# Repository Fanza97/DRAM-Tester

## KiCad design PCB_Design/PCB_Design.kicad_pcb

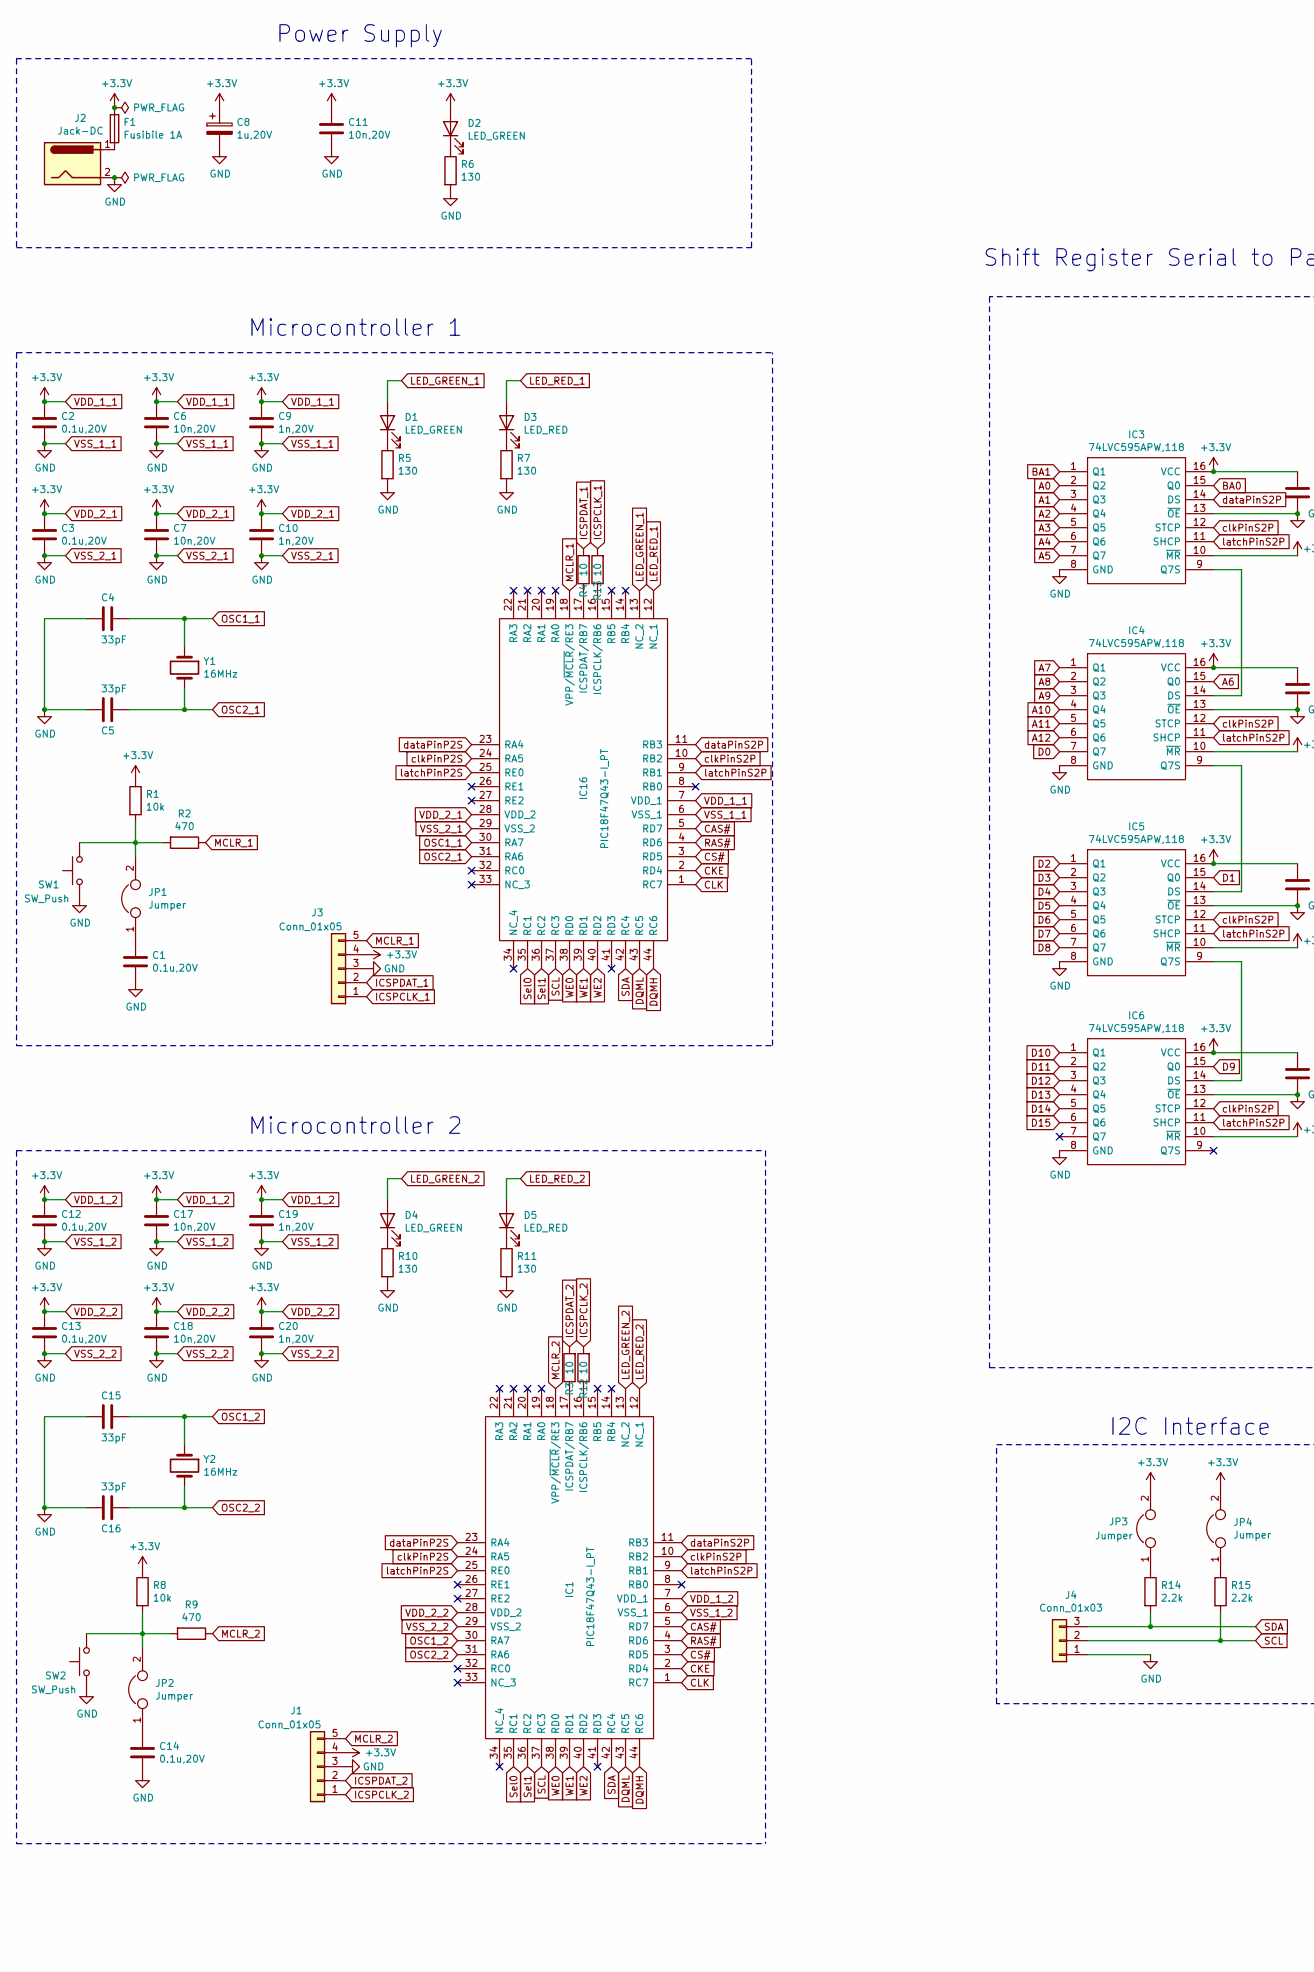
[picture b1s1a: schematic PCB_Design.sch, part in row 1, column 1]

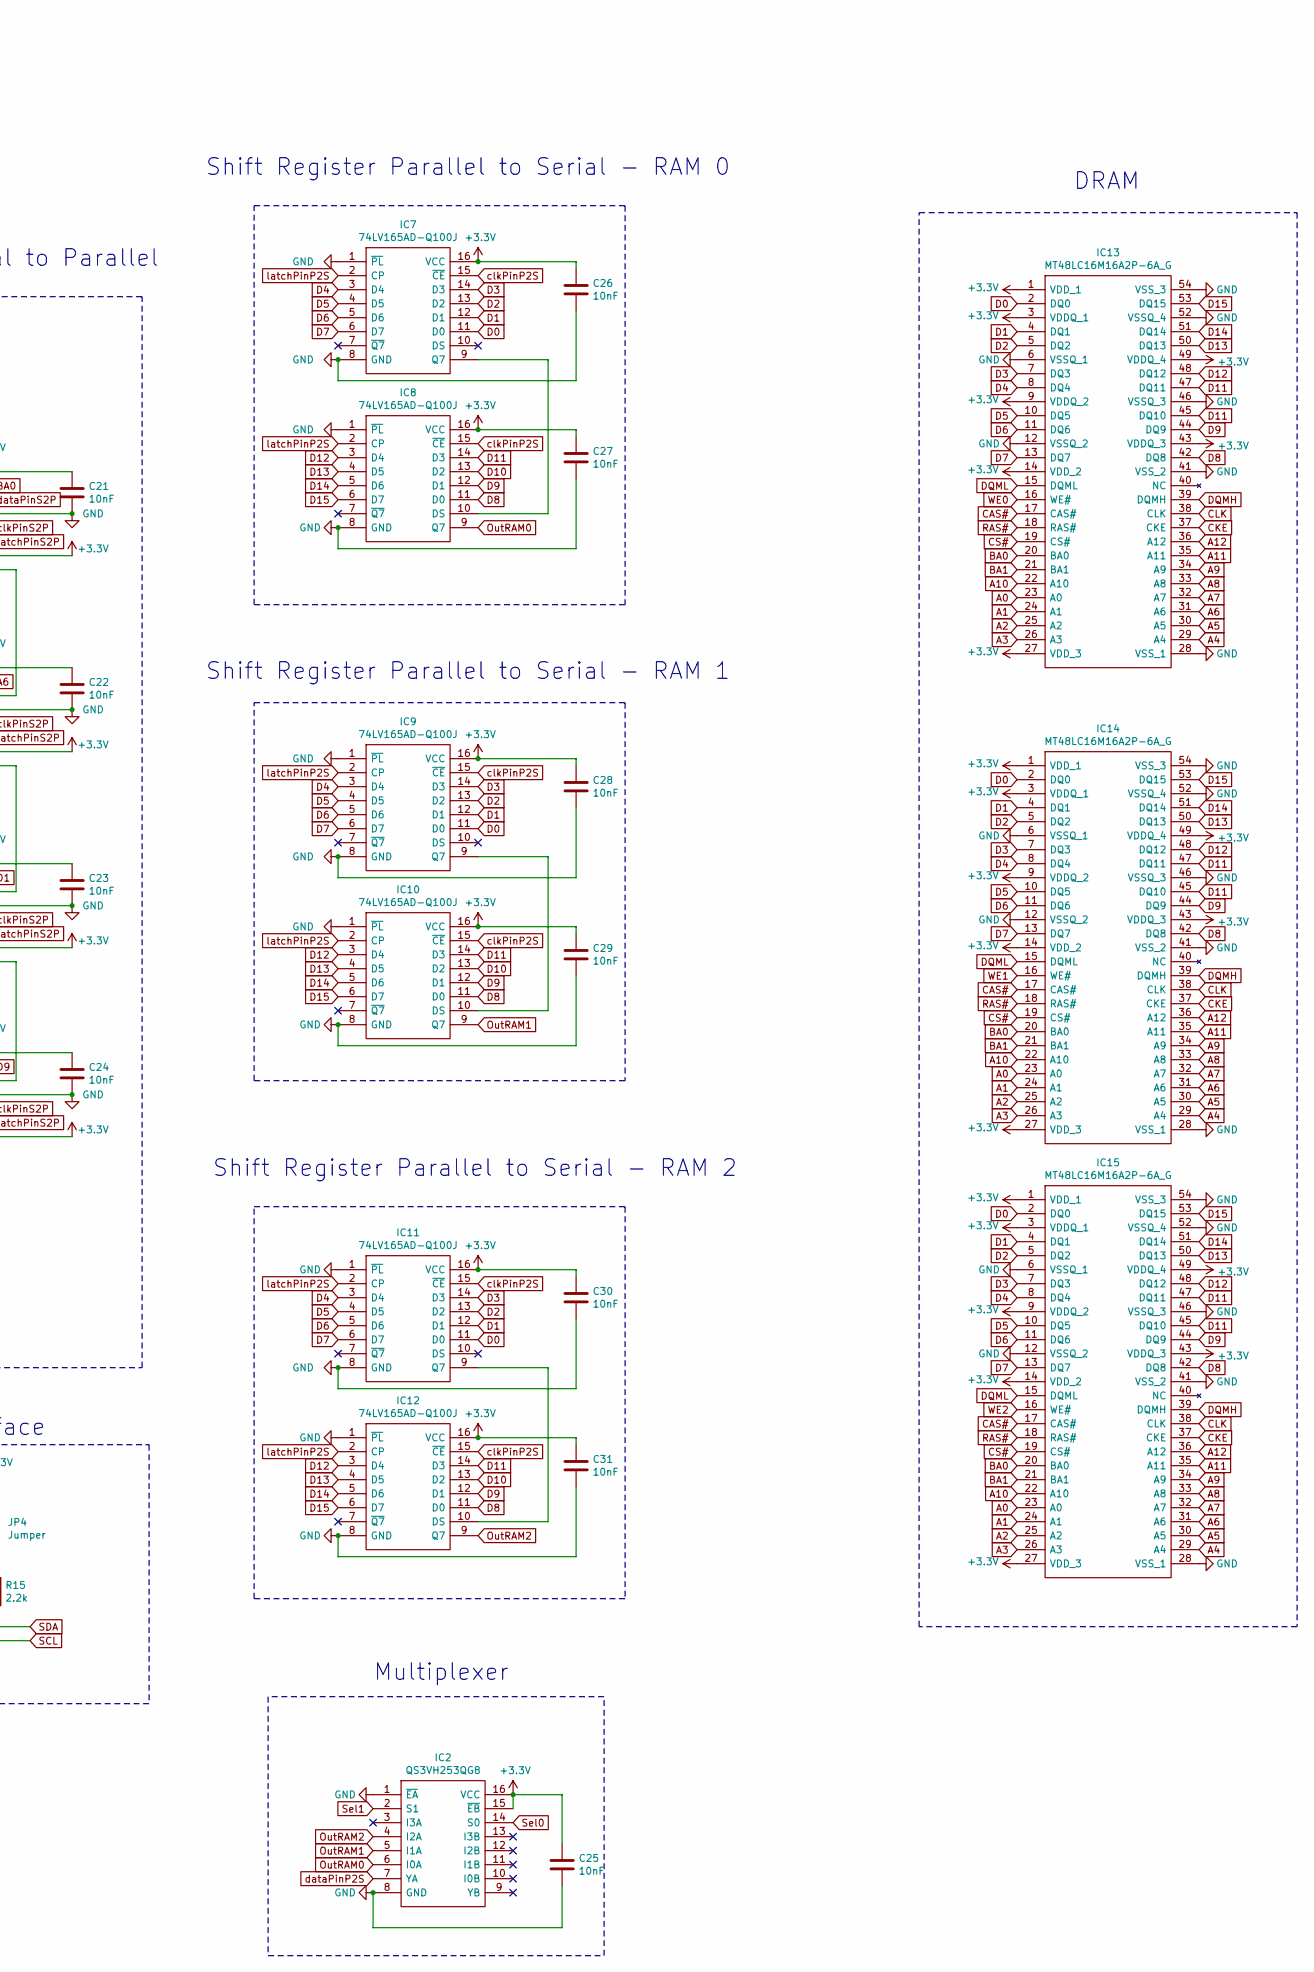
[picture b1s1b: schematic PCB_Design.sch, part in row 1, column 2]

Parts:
C1, C2, C3, C12, C13, C14: 0.1u,20V; C_0805_2012Metric_Pad1.15x1.40mm_HandSolder
C4, C5, C15, C16: 33pF; C_0805_2012Metric_Pad1.15x1.40mm_HandSolder
C6, C7, C11, C17, C18: 10n,20V; C_0805_2012Metric_Pad1.15x1.40mm_HandSolder
C8: 1u,20V; CP_Elec_4x4.5
C9, C10, C19, C20: 1n,20V; C_0805_2012Metric_Pad1.15x1.40mm_HandSolder
C21, C22, C23, C24, C25, C26, C27, C28, C29, C30, C31: 10nF; C_0805_2012Metric_Pad1.15x1.40mm_HandSolder
D1, D2, D4: LED_GREEN; LED_0805_2012Metric_Pad1.15x1.40mm_HandSolder
D3, D5: LED_RED; LED_0805_2012Metric_Pad1.15x1.40mm_HandSolder
F1: Fusibile 1A; Fuseholder_Cylinder-5x20mm_Schurter_0031_8201_Horizontal_Op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
IC1, IC16: PIC18F47Q43-I_PT; QFP80P1200X1200X120-44N; Mouser Part Number 579-PIC18F47Q43-I/PT
IC2: QS3VH253QG8; SOP64P602X173-16N; Mouser Part Number 972-QS3VH253QG8
IC3, IC4, IC5, IC6: 74LVC595APW,118; SOP65P640X110-16N; Mouser Part Number 771-LVC595APW118
IC7, IC8, IC9, IC10, IC11, IC12: 74LV165AD-Q100J; SOIC127P600X175-16N; Mouser Part Number 771-74LV165ADQ100J
IC13, IC14, IC15: MT48LC16M16A2P-6A_G; SOP80P1176X120-54N; Mouser Part Number 340-128308-TRAY
J1, J3: Conn_01x05; PinHeader_1x05_P2.54mm_Vertical
J2: Jack-DC; BarrelJack_CUI_PJ-063AH_Horizontal
J4: Conn_01x03; PinHeader_1x03_P2.54mm_Vertical
JP1, JP2, JP3, JP4: Jumper; TestPoint_Bridge_Pitch2.54mm_Drill1.0mm
R1, R8: 10k; R_0805_2012Metric_Pad1.15x1.40mm_HandSolder
R2, R9: 470; R_0805_2012Metric_Pad1.15x1.40mm_HandSolder
R3, R4, R12, R13: 10; R_0805_2012Metric_Pad1.15x1.40mm_HandSolder
R5, R6, R7, R10, R11: 130; R_0805_2012Metric_Pad1.15x1.40mm_HandSolder
R14, R15: 2.2k; R_0805_2012Metric_Pad1.15x1.40mm_HandSolder
SW1, SW2: SW_Push; SW_PUSH_6mm_H5mm
Y1, Y2: 16MHz; Crystal_SMD_HC49-SD

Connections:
A0: IC3.2 (Q2), IC13.23 (A0), IC14.23 (A0), IC15.23 (A0)
A1: IC3.3 (Q3), IC13.24 (A1), IC14.24 (A1), IC15.24 (A1)
A2: IC3.4 (Q4), IC13.25 (A2), IC14.25 (A2), IC15.25 (A2)
A3: IC3.5 (Q5), IC13.26 (A3), IC14.26 (A3), IC15.26 (A3)
A4: IC3.6 (Q6), IC13.29 (A4), IC14.29 (A4), IC15.29 (A4)
A5: IC3.7 (Q7), IC13.30 (A5), IC14.30 (A5), IC15.30 (A5)
A6: IC4.15 (Q0), IC13.31 (A6), IC14.31 (A6), IC15.31 (A6)
A7: IC4.1 (Q1), IC13.32 (A7), IC14.32 (A7), IC15.32 (A7)
A8: IC4.2 (Q2), IC13.33 (A8), IC14.33 (A8), IC15.33 (A8)
A9: IC4.3 (Q3), IC13.34 (A9), IC14.34 (A9), IC15.34 (A9)
A10: IC4.4 (Q4), IC13.22 (A10), IC14.22 (A10), IC15.22 (A10)
A11: IC4.5 (Q5), IC13.35 (A11), IC14.35 (A11), IC15.35 (A11)
A12: IC4.6 (Q6), IC13.36 (A12), IC14.36 (A12), IC15.36 (A12)
BA0: IC3.15 (Q0), IC13.20 (BA0), IC14.20 (BA0), IC15.20 (BA0)
BA1: IC3.1 (Q1), IC13.21 (BA1), IC14.21 (BA1), IC15.21 (BA1)
CAS#: IC1.5 (RD7), IC13.17 (CAS#), IC14.17 (CAS#), IC15.17 (CAS#), IC16.5 (RD7)
CKE: IC1.2 (RD4), IC13.37 (CKE), IC14.37 (CKE), IC15.37 (CKE), IC16.2 (RD4)
CLK: IC1.1 (RC7), IC13.38 (CLK), IC14.38 (CLK), IC15.38 (CLK), IC16.1 (RC7)
CS#: IC1.3 (RD5), IC13.19 (CS#), IC14.19 (CS#), IC15.19 (CS#), IC16.3 (RD5)
D0: IC4.7 (Q7), IC7.11 (D0), IC9.11 (D0), IC11.11 (D0), IC13.2 (DQ0), IC14.2 (DQ0), IC15.2 (DQ0)
D1: IC5.15 (Q0), IC7.12 (D1), IC9.12 (D1), IC11.12 (D1), IC13.4 (DQ1), IC14.4 (DQ1), IC15.4 (DQ1)
D2: IC5.1 (Q1), IC7.13 (D2), IC9.13 (D2), IC11.13 (D2), IC13.5 (DQ2), IC14.5 (DQ2), IC15.5 (DQ2)
D3: IC5.2 (Q2), IC7.14 (D3), IC9.14 (D3), IC11.14 (D3), IC13.7 (DQ3), IC14.7 (DQ3), IC15.7 (DQ3)
D4: IC5.3 (Q3), IC7.3 (D4), IC9.3 (D4), IC11.3 (D4), IC13.8 (DQ4), IC14.8 (DQ4), IC15.8 (DQ4)
D5: IC5.4 (Q4), IC7.4 (D5), IC9.4 (D5), IC11.4 (D5), IC13.10 (DQ5), IC14.10 (DQ5), IC15.10 (DQ5)
D6: IC5.5 (Q5), IC7.5 (D6), IC9.5 (D6), IC11.5 (D6), IC13.11 (DQ6), IC14.11 (DQ6), IC15.11 (DQ6)
D7: IC5.6 (Q6), IC7.6 (D7), IC9.6 (D7), IC11.6 (D7), IC13.13 (DQ7), IC14.13 (DQ7), IC15.13 (DQ7)
D8: IC5.7 (Q7), IC8.11 (D0), IC10.11 (D0), IC12.11 (D0), IC13.42 (DQ8), IC14.42 (DQ8), IC15.42 (DQ8)
D9: IC6.15 (Q0), IC8.12 (D1), IC10.12 (D1), IC12.12 (D1), IC13.44 (DQ9), IC14.44 (DQ9), IC15.44 (DQ9)
D10: IC6.1 (Q1), IC8.13 (D2), IC10.13 (D2), IC12.13 (D2)
D11: IC6.2 (Q2), IC8.14 (D3), IC10.14 (D3), IC12.14 (D3), IC13.45 (DQ10), IC13.47 (DQ11), IC14.45 (DQ10), IC14.47 (DQ11), IC15.45 (DQ10), IC15.47 (DQ11)
D12: IC6.3 (Q3), IC8.3 (D4), IC10.3 (D4), IC12.3 (D4), IC13.48 (DQ12), IC14.48 (DQ12), IC15.48 (DQ12)
D13: IC6.4 (Q4), IC8.4 (D5), IC10.4 (D5), IC12.4 (D5), IC13.50 (DQ13), IC14.50 (DQ13), IC15.50 (DQ13)
D14: IC6.5 (Q5), IC8.5 (D6), IC10.5 (D6), IC12.5 (D6), IC13.51 (DQ14), IC14.51 (DQ14), IC15.51 (DQ14)
D15: IC6.6 (Q6), IC8.6 (D7), IC10.6 (D7), IC12.6 (D7), IC13.53 (DQ15), IC14.53 (DQ15), IC15.53 (DQ15)
DQMH: IC1.44 (RC6), IC13.39 (DQMH), IC14.39 (DQMH), IC15.39 (DQMH), IC16.44 (RC6)
DQML: IC1.43 (RC5), IC13.15 (DQML), IC14.15 (DQML), IC15.15 (DQML), IC16.43 (RC5)
ICSPCLK_1: J3.1, R13.2
ICSPCLK_2: J1.1, R12.2
ICSPDAT_1: J3.2, R4.2
ICSPDAT_2: J1.2, R3.2
LED_GREEN_1: D1.2 (A), IC16.13 (NC_2)
LED_GREEN_2: D4.2 (A), IC1.13 (NC_2)
LED_RED_1: D3.2 (A), IC16.12 (NC_1)
LED_RED_2: D5.2 (A), IC1.12 (NC_1)
MCLR_1: IC16.18 (VPP/~MCLR~/RE3), J3.5, R2.1
MCLR_2: IC1.18 (VPP/~MCLR~/RE3), J1.5, R9.1
unnamed: C1.2, JP1.1
unnamed: C14.2, JP2.1
unnamed: D1.1 (K), R5.1
unnamed: D2.1 (K), R6.1
unnamed: D3.1 (K), R7.1
unnamed: D4.1 (K), R10.1
unnamed: D5.1 (K), R11.1
unnamed: F1.2, J2.1
unnamed: IC1.16 (ICSPCLK/RB6), R12.1
unnamed: IC1.17 (ICSPDAT/RB7), R3.1
unnamed: IC3.9 (Q7S), IC4.14 (DS)
unnamed: IC4.9 (Q7S), IC5.14 (DS)
unnamed: IC5.9 (Q7S), IC6.14 (DS)
unnamed: IC7.9 (Q7), IC8.10 (DS)
unnamed: IC9.9 (Q7), IC10.10 (DS)
unnamed: IC11.9 (Q7), IC12.10 (DS)
unnamed: IC16.16 (ICSPCLK/RB6), R13.1
unnamed: IC16.17 (ICSPDAT/RB7), R4.1
unnamed: JP1.2, R1.2, R2.2, SW1.2
unnamed: JP2.2, R8.2, R9.2, SW2.2
unnamed: JP3.1, R14.1
unnamed: JP4.1, R15.1
OSC1_1: C4.2, IC16.30 (RA7), Y1.1
OSC1_2: C15.2, IC1.30 (RA7), Y2.1
OSC2_1: C5.2, IC16.31 (RA6), Y1.2
OSC2_2: C16.2, IC1.31 (RA6), Y2.2
OutRAM0: IC2.6 (I0A), IC8.9 (Q7)
OutRAM1: IC2.5 (I1A), IC10.9 (Q7)
OutRAM2: IC2.4 (I2A), IC12.9 (Q7)
RAS#: IC1.4 (RD6), IC13.18 (RAS#), IC14.18 (RAS#), IC15.18 (RAS#), IC16.4 (RD6)
SCL: IC1.37 (RC3), IC16.37 (RC3), J4.2, R15.2
SDA: IC1.42 (RC4), IC16.42 (RC4), J4.3, R14.2
Sel0: IC1.35 (RC1), IC2.14 (S0), IC16.35 (RC1)
Sel1: IC1.36 (RC2), IC2.2 (S1), IC16.36 (RC2)
VDD_1_1: C2.2, C3.2, C6.2, C7.2, C8.1, C9.2, C10.2, C11.2, C12.2, C13.2, C17.2, C18.2, C19.2, C20.2, C21.1, C22.1, C23.1, C24.1, C25.1, C26.1, C27.1, C28.1, C29.1, C30.1, C31.1, D2.2 (A), F1.1, IC1.7 (VDD_1), IC1.28 (VDD_2), IC2.15 (~EB), IC2.16 (VCC), IC3.10 (~MR), IC3.16 (VCC), IC4.10 (~MR), IC4.16 (VCC), IC5.10 (~MR), IC5.16 (VCC), IC6.10 (~MR), IC6.16 (VCC), IC7.16 (VCC), IC8.16 (VCC), IC9.16 (VCC), IC10.16 (VCC), IC11.16 (VCC), IC12.16 (VCC), IC13.1 (VDD_1), IC13.3 (VDDQ_1), IC13.9 (VDDQ_2), IC13.14 (VDD_2), IC13.27 (VDD_3), IC13.43 (VDDQ_3), IC13.49 (VDDQ_4), IC14.1 (VDD_1), IC14.3 (VDDQ_1), IC14.9 (VDDQ_2), IC14.14 (VDD_2), IC14.27 (VDD_3), IC14.43 (VDDQ_3), IC14.49 (VDDQ_4), IC15.1 (VDD_1), IC15.3 (VDDQ_1), IC15.9 (VDDQ_2), IC15.14 (VDD_2), IC15.27 (VDD_3), IC15.43 (VDDQ_3), IC15.49 (VDDQ_4), IC16.7 (VDD_1), IC16.28 (VDD_2), J1.4, J3.4, JP3.2, JP4.2, R1.1, R8.1
VSS_1_1: C1.1, C2.1, C3.1, C4.1, C5.1, C6.1, C7.1, C8.2, C9.1, C10.1, C11.1, C12.1, C13.1, C14.1, C15.1, C16.1, C17.1, C18.1, C19.1, C20.1, C21.2, C22.2, C23.2, C24.2, C25.2, C26.2, C27.2, C28.2, C29.2, C30.2, C31.2, IC1.6 (VSS_1), IC1.29 (VSS_2), IC2.1 (~EA), IC2.8 (GND), IC3.8 (GND), IC3.13 (~OE), IC4.8 (GND), IC4.13 (~OE), IC5.8 (GND), IC5.13 (~OE), IC6.8 (GND), IC6.13 (~OE), IC7.1 (~PL), IC7.8 (GND), IC8.1 (~PL), IC8.8 (GND), IC9.1 (~PL), IC9.8 (GND), IC10.1 (~PL), IC10.8 (GND), IC11.1 (~PL), IC11.8 (GND), IC12.1 (~PL), IC12.8 (GND), IC13.6 (VSSQ_1), IC13.12 (VSSQ_2), IC13.28 (VSS_1), IC13.41 (VSS_2), IC13.46 (VSSQ_3), IC13.52 (VSSQ_4), IC13.54 (VSS_3), IC14.6 (VSSQ_1), IC14.12 (VSSQ_2), IC14.28 (VSS_1), IC14.41 (VSS_2), IC14.46 (VSSQ_3), IC14.52 (VSSQ_4), IC14.54 (VSS_3), IC15.6 (VSSQ_1), IC15.12 (VSSQ_2), IC15.28 (VSS_1), IC15.41 (VSS_2), IC15.46 (VSSQ_3), IC15.52 (VSSQ_4), IC15.54 (VSS_3), IC16.6 (VSS_1), IC16.29 (VSS_2), J1.3, J2.2, J3.3, J4.1, R5.2, R6.2, R7.2, R10.2, R11.2, SW1.1, SW2.1
WE0: IC1.38 (RD0), IC13.16 (WE#), IC16.38 (RD0)
WE1: IC1.39 (RD1), IC14.16 (WE#), IC16.39 (RD1)
WE2: IC1.40 (RD2), IC15.16 (WE#), IC16.40 (RD2)
clkPinP2S: IC1.24 (RA5), IC7.15 (~CE), IC8.15 (~CE), IC9.15 (~CE), IC10.15 (~CE), IC11.15 (~CE), IC12.15 (~CE), IC16.24 (RA5)
clkPinS2P: IC1.10 (RB2), IC3.12 (STCP), IC4.12 (STCP), IC5.12 (STCP), IC6.12 (STCP), IC16.10 (RB2)
dataPinP2S: IC1.23 (RA4), IC2.7 (YA), IC16.23 (RA4)
dataPinS2P: IC1.11 (RB3), IC3.14 (DS), IC16.11 (RB3)
latchPinP2S: IC1.25 (RE0), IC7.2 (CP), IC8.2 (CP), IC9.2 (CP), IC10.2 (CP), IC11.2 (CP), IC12.2 (CP), IC16.25 (RE0)
latchPinS2P: IC1.9 (RB1), IC3.11 (SHCP), IC4.11 (SHCP), IC5.11 (SHCP), IC6.11 (SHCP), IC16.9 (RB1)

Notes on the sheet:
Shift Register Serial to Parallel
Shift Register Parallel to Serial - RAM 0
Shift Register Parallel to Serial - RAM 1
Shift Register Parallel to Serial - RAM 2
DRAM
Multiplexer
Microcontroller 1
Power Supply
Microcontroller 2
I2C Interface

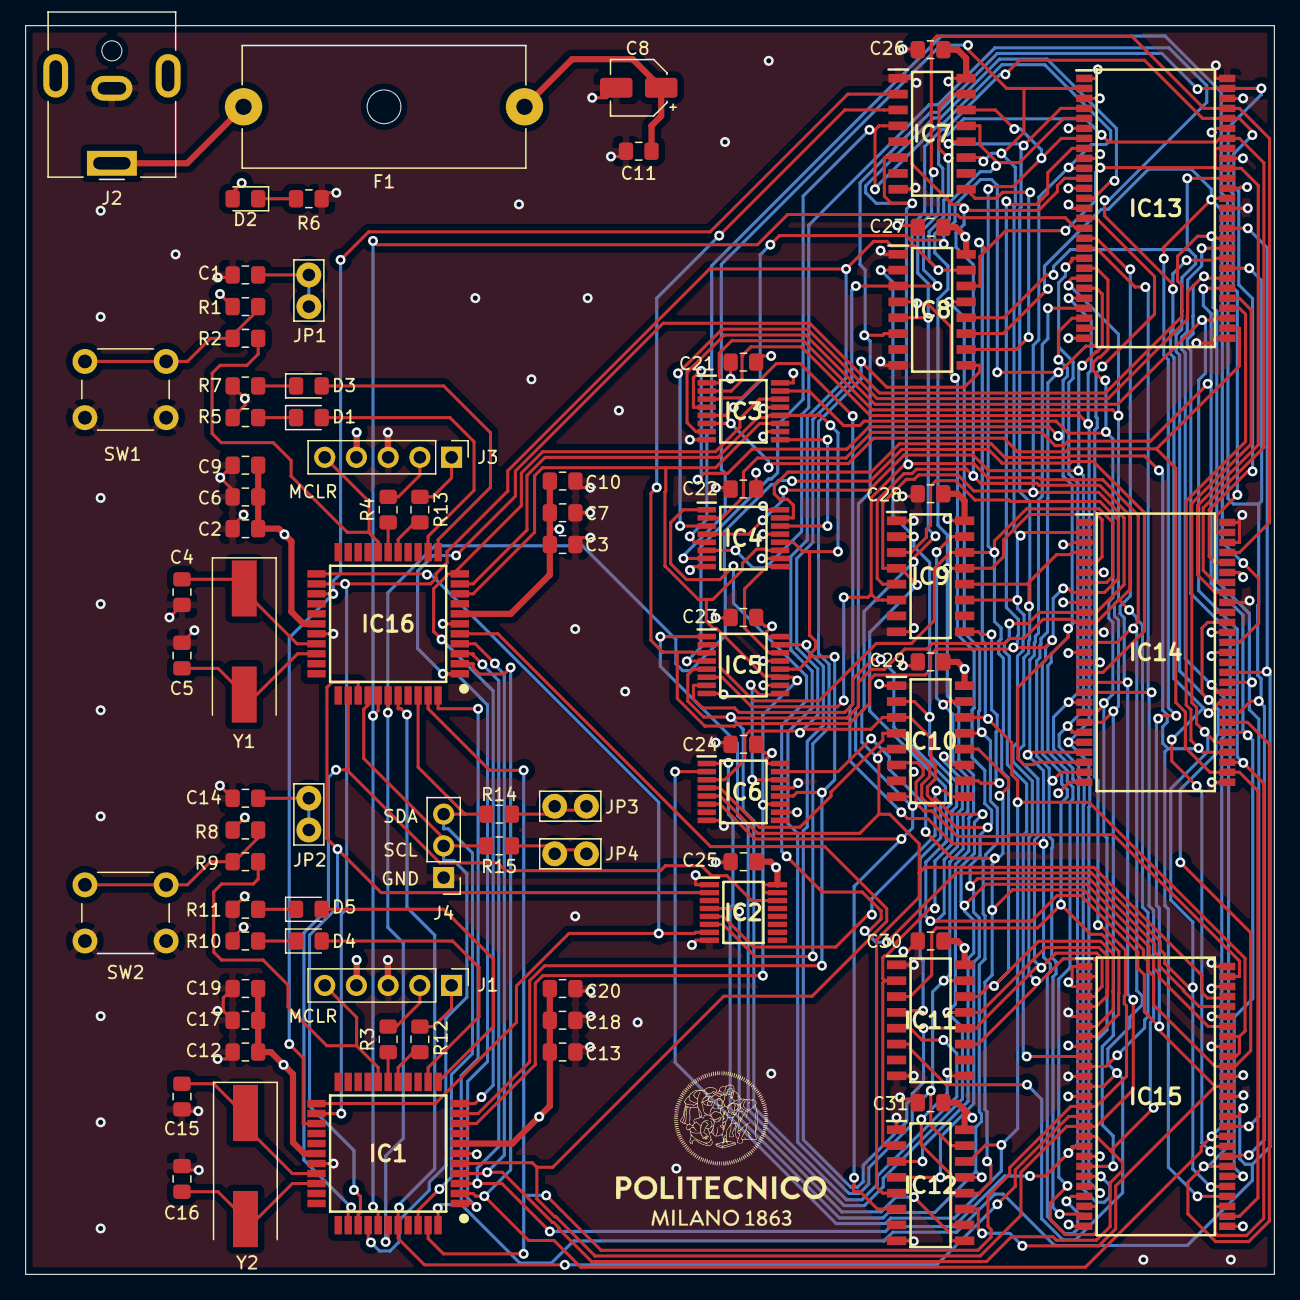
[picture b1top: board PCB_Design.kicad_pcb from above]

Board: 4 copper layers, 100.0 x 100.0 mm, 80 parts (0 on the bottom side), 92 nets.
